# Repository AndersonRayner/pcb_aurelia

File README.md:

# Aurelia X6 Custom Boards
PCBs for use on Aurelia X6 Hexacopter.

The [Aurelia X6](https://uavsystemsinternational.com/products/aurelia-x6-standard) is great, but sometimes you just want to modify your hardware and do new things with it. 

```
These aren't finished yet, so make sure to finish them as required if you plan on using them.
```

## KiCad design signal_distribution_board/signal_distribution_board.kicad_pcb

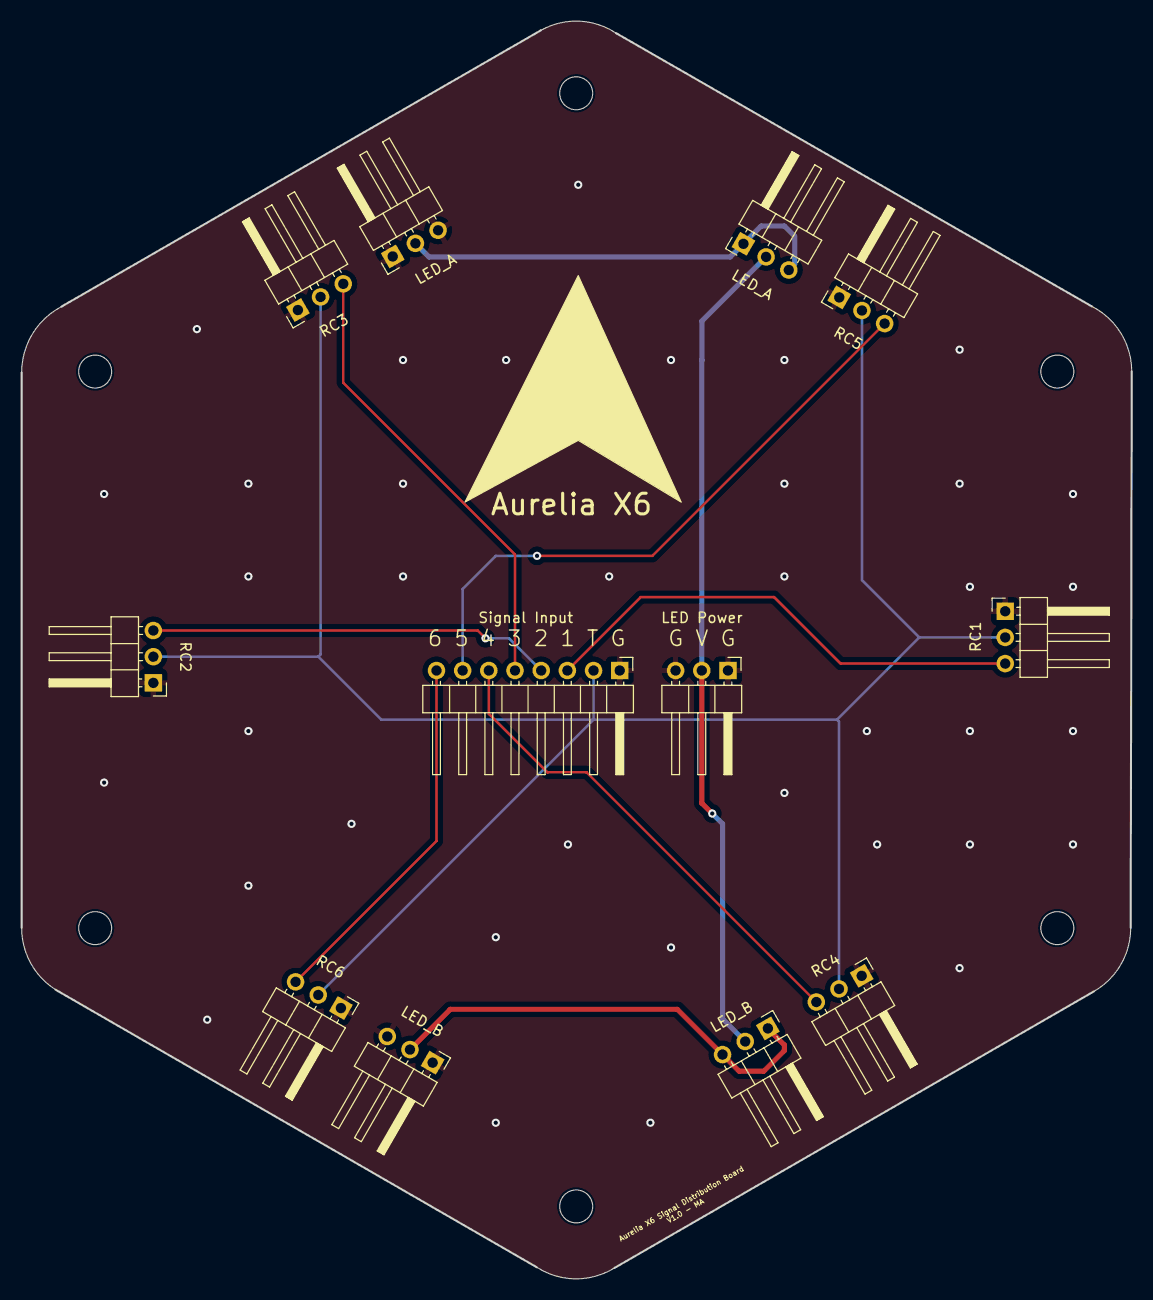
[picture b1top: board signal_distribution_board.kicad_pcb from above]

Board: 2 copper layers, 107.7 x 122.0 mm, 18 parts (0 on the bottom side), 11 nets.

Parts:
H1, H2, H3, H4, H5, H6: MountingHole; MountingHole_3.2mm_M3
J1: RC1; PinHeader_1x03_P2.54mm_Horizontal
J2: RC2; PinHeader_1x03_P2.54mm_Horizontal
J3: RC3; PinHeader_1x03_P2.54mm_Horizontal
J4: RC4; PinHeader_1x03_P2.54mm_Horizontal
J5: RC5; PinHeader_1x03_P2.54mm_Horizontal
J6: RC6; PinHeader_1x03_P2.54mm_Horizontal
J7: Signal Input; PinHeader_1x08_P2.54mm_Horizontal
J8, J11: LED_A; PinHeader_1x03_P2.54mm_Horizontal
J9, J12: LED_B; PinHeader_1x03_P2.54mm_Horizontal
J10: LED Power; PinHeader_1x03_P2.54mm_Horizontal

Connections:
/LED_PWR: J9.2, J10.2, J11.2
Earth: J1.1, J2.1, J3.1, J4.1, J5.1, J6.1, J7.1, J8.1, J8.3, J10.1, J10.3, J12.1, J12.3
unnamed: J1.2, J2.2, J3.2, J4.2, J5.2, J6.2, J7.2
unnamed: J1.3, J7.3
unnamed: J2.3, J7.4
unnamed: J3.3, J7.5
unnamed: J4.3, J7.6
unnamed: J5.3, J7.7
unnamed: J6.3, J7.8
unnamed: J8.2, J11.1, J11.3
unnamed: J9.1, J9.3, J12.2

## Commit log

2024-01-20 Updates to board routing
2024-01-22 Version for production
